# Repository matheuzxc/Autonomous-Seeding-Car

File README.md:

# Autonomous-Seeding-Car

Este projeto visa o desenvolvimento de um veículo remotamente controlado com controle de velocidade variável e navegação autônoma até coordenadas pré-definidas. A funcionalidade adicional será a simulação de uma semeadora automatizada, abordando desafios de sincronização mecânica-eletrônica e mapeamento georreferenciado.

## Metodologia

A metodologia adotada para o desenvolvimento do **Autonomous-Seeding-Car** foca na criação de um sistema autônomo e preciso, que integra controle de navegação, movimentação e semeadura em um veículo de baixo custo. A estrutura metodológica do projeto é composta pelas seguintes etapas principais:

### 1. **Navegação Autônoma**

A navegação do carrinho é baseada em coordenadas geográficas. O veículo utiliza um sistema de GPS para determinar sua posição e calcular a direção necessária para alcançar um destino pré-definido. A direção do carrinho é continuamente corrigida utilizando uma bússola digital, que fornece a orientação do veículo em relação ao norte magnético.

Além disso, o movimento é controlado dinamicamente com base em um sistema de controle, que ajusta a velocidade e a direção das rodas para garantir que o carrinho siga a trajetória desejada. A navegação é baseada na conversão das coordenadas geográficas em distâncias e ângulos de deslocamento, minimizando erros ao longo do caminho.

### 2. **Controle de Velocidade e Deslocamento**

O sistema de controle utiliza um controlador proporcional-integral-derivativo (PID) para ajustar a velocidade e direção do carrinho, de forma a evitar oscilações e garantir uma movimentação suave e precisa. O PID ajuda a manter o carrinho na trajetória correta, mesmo em condições variáveis ou imprecisas de movimentação, resultando em uma navegação mais estável e controlada.

### 3. **Execução da Semeadura**

Quando o carrinho chega ao ponto de destino, o processo de semeadura é automaticamente acionado. O carrinho se move em um padrão sistemático, alternando entre deslocamentos lineares e laterais para cobrir a área predeterminada para semeadura. Durante esses movimentos, o sistema de dispersão libera as sementes de maneira uniforme, assegurando que a operação de semeadura seja realizada de forma eficiente e precisa.

### 4. **Integração Mecânica e Eletrônica**

O projeto envolve desafios significativos de sincronização entre a mecânica e a eletrônica, especialmente na operação do sistema de semeadura e controle de movimentação. O ajuste contínuo de posição e direção, bem como o controle preciso do sistema de semeadura, são feitos de forma coordenada para garantir que as sementes sejam liberadas no momento e local corretos.

### 5. **Mapeamento Georreferenciado**

A navegação do carrinho é suportada por um mapeamento georreferenciado, que permite ao veículo seguir coordenadas pré-definidas, assegurando a cobertura adequada da área. A utilização de dados geoespaciais ajuda a garantir que o carrinho execute a semeadura de forma precisa, mapeando de forma eficiente os locais onde as sementes devem ser dispersas.

---

## Arcadia e Capella

Para o desenvolvimento do projeto, foi utilizada a **metodologia Arcadia** juntamente com a ferramenta **Capella**, ambas voltadas para a modelagem de sistemas complexos.

### Arcadia

**Arcadia** (Architecture Analysis & Design Integrated Approach) é uma metodologia estruturada para a análise e o design de sistemas complexos. Ela permite modelar, definir e validar os requisitos, projetar a arquitetura do sistema e garantir que todos os elementos funcionem de forma coerente e integrada.

A metodologia Arcadia segue um fluxo de camadas, cada uma abordando um aspecto específico do sistema:

1. **Operational Analysis (OA)**: Define as necessidades dos usuários e as operações gerais do sistema.
2. **System Analysis (SA)**: Especifica o que o sistema deve fazer, sem entrar nos detalhes de implementação.
3. **Logical Architecture (LA)**: Estrutura o sistema em componentes lógicos, definindo suas interações.
4. **Physical Architecture (PA)**: Foca na implementação real, especificando o hardware, software e interfaces.

Para o **Autonomous-Seeding-Car**, foi adotada a **camada de Arquitetura Física**, dado o prazo de desenvolvimento ágil e a necessidade de implementação prática dentro de um tempo limitado. Esta camada descreve todos os componentes físicos e suas interações no sistema, garantindo que a arquitetura final seja viável e eficiente.

### Capella

**Capella** é a ferramenta de modelagem baseada na metodologia Arcadia. Ela permite criar diagramas, definir requisitos, especificar as interações entre os módulos e gerar a arquitetura do sistema. Capella proporciona uma visão clara e estruturada de como o sistema será implementado, facilitando a análise e o design, além de garantir a consistência entre os diferentes componentes.

Com Capella, a arquitetura física do **Autonomous-Seeding-Car** foi modelada e validada, permitindo o desenvolvimento e implementação eficiente de todos os módulos do sistema, desde a navegação até a semeadura automatizada.

---

## Diagramas do Sistema

Abaixo estão os diagramas explicativos que foram usados para modelar a arquitetura do sistema no **Capella**.

### Bloco de Componente na Arquitetura Física

Este diagrama mostra os principais blocos de componentes na arquitetura física do **Autonomous-Seeding-Car**, representando os módulos de hardware e suas interações.

### Arquitetura Final

O diagrama abaixo mostra a arquitetura final do sistema, com os componentes integrados e suas conexões, tanto físicas quanto lógicas. Ele ilustra como os diferentes módulos interagem para formar o sistema completo.

---

Com essa abordagem metodológica e a utilização das ferramentas Arcadia e Capella, o projeto **Autonomous-Seeding-Car** é desenvolvido de forma organizada e eficaz, garantindo que todos os componentes funcionem de maneira integrada e otimizando o processo de navegação e semeadura do veículo.

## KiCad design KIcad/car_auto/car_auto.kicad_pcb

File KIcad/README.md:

# PCB do Sistema Eletrônico - **Autonomous-Seeding-Car**

Este repositório contém as PCBs (Placas de Circuito Impresso) que compõem os módulos eletrônicos do projeto **Autonomous-Seeding-Car**. O sistema eletrônico é composto por três PCBs empilhadas verticalmente, cada uma responsável por um conjunto específico de funções dentro do sistema. As PCBs foram projetadas no **KiCad**, com o objetivo de criar um design eficiente e compactado, garantindo a integração correta dos módulos eletrônicos.

## Estrutura das PCBs

A estrutura do sistema é organizada em três PCBs interconectadas, uma em cima da outra, de forma a otimizar o uso de espaço e a organização dos componentes. Cada PCB desempenha um papel crucial no funcionamento geral do carrinho autônomo. As PCBs são distribuídas conforme descrito abaixo:

### PCB 1: Módulo Regulador de Tensão e Ponte H

A primeira PCB contém os seguintes módulos eletrônicos:

- **Módulo Regulador de Tensão (LM2596)**: Responsável por fornecer a tensão estável necessária para os outros módulos do sistema, garantindo que os componentes eletrônicos operem de forma segura e eficiente.
- **Ponte H Dupla (L298N)**: Controla os motores do veículo, regulando a direção e velocidade com base nos comandos enviados pelo ESP32. Este módulo é essencial para o controle de movimentação do carrinho.

### PCB 2: ESP32 e Módulo Bluetooth

A segunda PCB contém os seguintes componentes:

- **ESP32 WROOM**: O microcontrolador central do sistema, que coordena a comunicação entre os diferentes módulos e processa os comandos para controle de movimento e semeadura.
- **Módulo Bluetooth HC-05**: Responsável pela comunicação sem fio com o controle remoto, permitindo que o carrinho seja operado remotamente. Recebe comandos de movimentação e transmite-os ao ESP32 para execução.

### PCB 3: Módulo GPS

A terceira PCB contém o **Módulo GPS NEO-6M**, responsável por fornecer a localização geográfica do carrinho. Ele permite que o veículo se desloque até coordenadas pré-definidas com precisão, essencial para a navegação autônoma.

### Montagem Final das 3 PCBs

As 3 PCBs foram projetadas para serem empilhadas verticalmente, com uma em cima da outra. A disposição otimiza o uso do espaço e facilita a integração dos módulos. Abaixo, está a foto da montagem final das 3 PCBs conectadas.

### Posicionamento da Bússola

A **bússola (HMC5883L)** está posicionada na frente do carro, fora da pilha de PCBs. Ela é responsável por fornecer a direção do carrinho em relação ao norte magnético, permitindo que o sistema ajuste a orientação de forma precisa.

---

## Pinos de Conexão no ESP32

Abaixo estão os pinos utilizados para cada módulo no ESP32:

| **Módulo**           | **Pinos no ESP32**                               |
|----------------------|--------------------------------------------------|
| **GPS (NEO-6M)**      | RX2 → GPIO 16, TX2 → GPIO 17                    |
| **Bússola/IMU**       | SDA → GPIO 21, SCL → GPIO 22                    |
| **Ponte H (Motores)** | IN1 → GPIO 25, IN2 → GPIO 26, IN3 → GPIO 27, IN4 → GPIO 14, PWM A → GPIO 32, PWM B → GPIO 33 |
| **Bluetooth (HC-05)** | RX1 → GPIO 4, TX1 → GPIO 2                      |
| **Servo Motor**       | Sinal → GPIO 13                                 |

---

## Design no KiCad

Todas as PCBs foram projetadas no **KiCad**, uma ferramenta open-source poderosa para o design de circuitos eletrônicos e PCBs. O design foi otimizado para garantir um layout compacto, com o mínimo de interferências entre os componentes e com uma conexão eficiente entre as diferentes placas.

---

## Contribuições

Contribuições para este projeto são bem-vindas! Caso deseje sugerir melhorias no design ou no código, fique à vontade para abrir um **pull request**.

---

## Licença

Este projeto está licenciado sob a licença **MIT**. Consulte o arquivo LICENSE para mais detalhes.

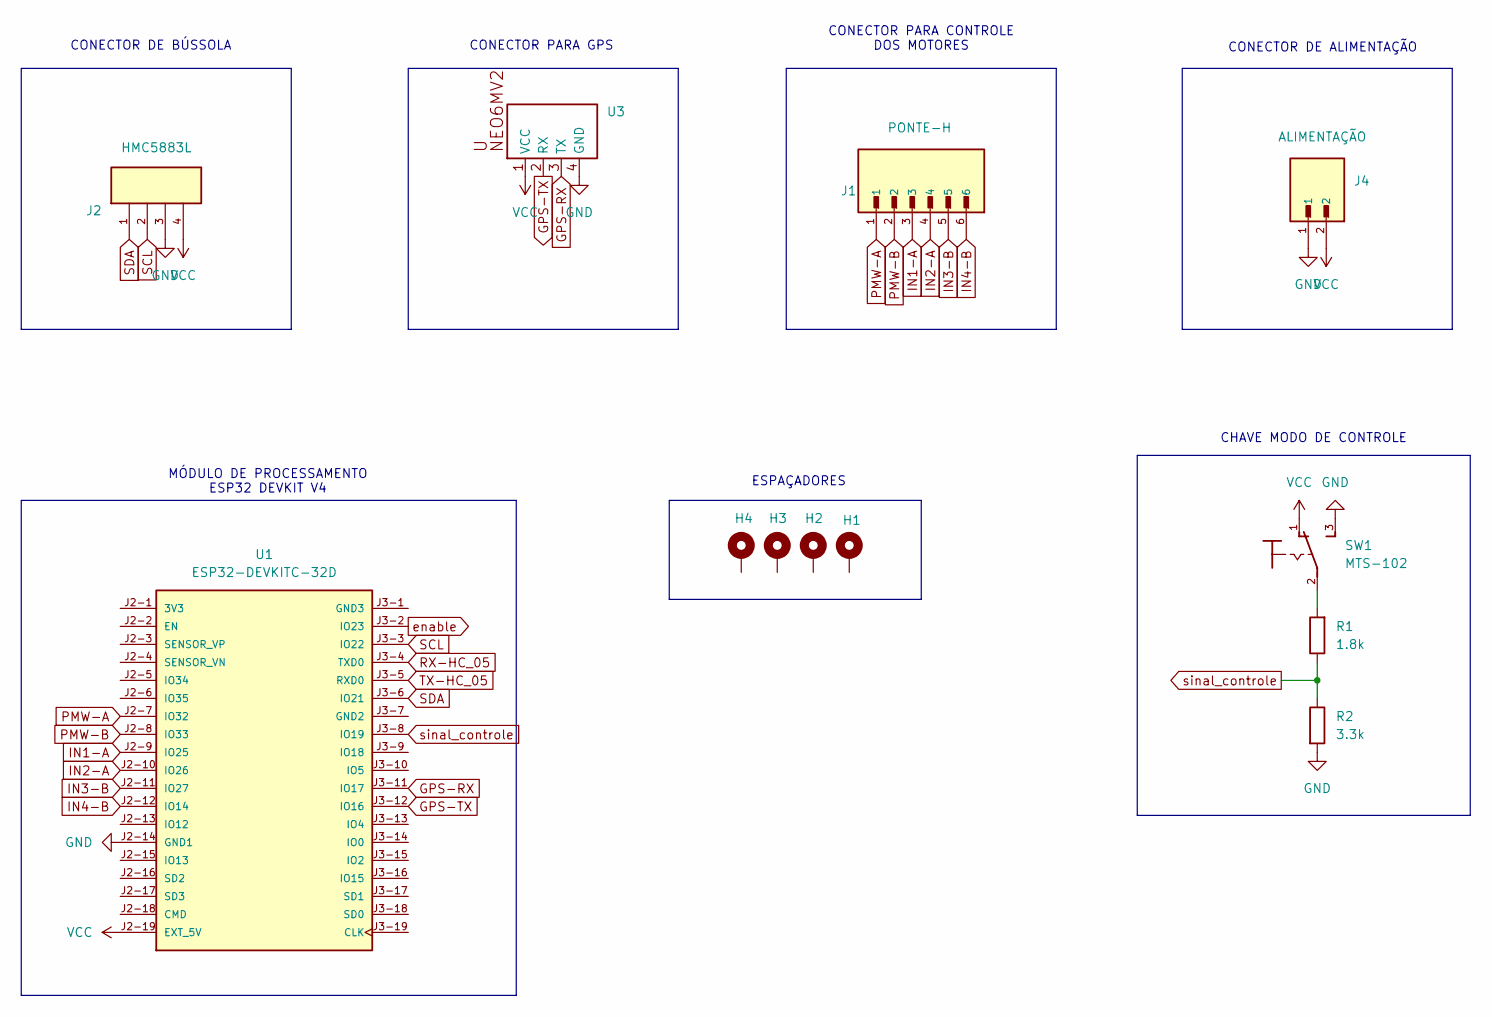
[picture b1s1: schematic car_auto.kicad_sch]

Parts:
H1, H2, H3, H4: MountingHole_Pad; MountingHole_3.2mm_M3_DIN965_Pad
J1: PONTE-H; JST_B6P-VH_LF__SN_
J2: HMC5883L; JST_B4P-VH_LF__SN_
J4: ALIMENTAÇÃO; JST_B2P-VH_LF__SN_
R1: 1.8k; R_Axial_DIN0207_L6.3mm_D2.5mm_P10.16mm_Horizontal
R2: 3.3k; R_Axial_DIN0207_L6.3mm_D2.5mm_P10.16mm_Horizontal
SW1: MTS-102
U1: ESP32-DEVKITC-32D; MODULE_ESP32-DEVKITC-32D; PARTREV V4
U3: NEO-6M-V2-GPSMODULE-FOOTPRINT

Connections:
GND: J2.3, J4.1, R2.2, SW1.3, U1.J2-14 (GND1), U3.4 (GND)
GPS-RX: U1.J3-11 (IO17), U3.3 (TX)
GPS-TX: U1.J3-12 (IO16), U3.2 (RX)
IN1-A: J1.3, U1.J2-9 (IO25)
IN2-A: J1.4, U1.J2-10 (IO26)
IN3-B: J1.5, U1.J2-11 (IO27)
IN4-B: J1.6, U1.J2-12 (IO14)
unnamed: R1.2, SW1.2
PMW-A: J1.1, U1.J2-7 (IO32)
PMW-B: J1.2, U1.J2-8 (IO33)
RX-HC_05: U1.J3-4 (TXD0)
SCL: J2.2, U1.J3-3 (IO22)
SDA: J2.1, U1.J3-6 (IO21)
TX-HC_05: U1.J3-5 (RXD0)
VCC: J2.4, J4.2, SW1.1, U1.J2-19 (EXT_5V), U3.1 (VCC)
enable: U1.J3-2 (IO23)
sinal_controle: R1.1, R2.1, U1.J3-8 (IO19)

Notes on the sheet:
CONECTOR PARA GPS
MÓDULO DE PROCESSAMENTO ESP32 DEVKIT V4
CONECTOR PARA CONTROLE DOS MOTORES
ESPAÇADORES
CONECTOR DE BÚSSOLA
CONECTOR DE ALIMENTAÇÃO
CHAVE MODO DE CONTROLE

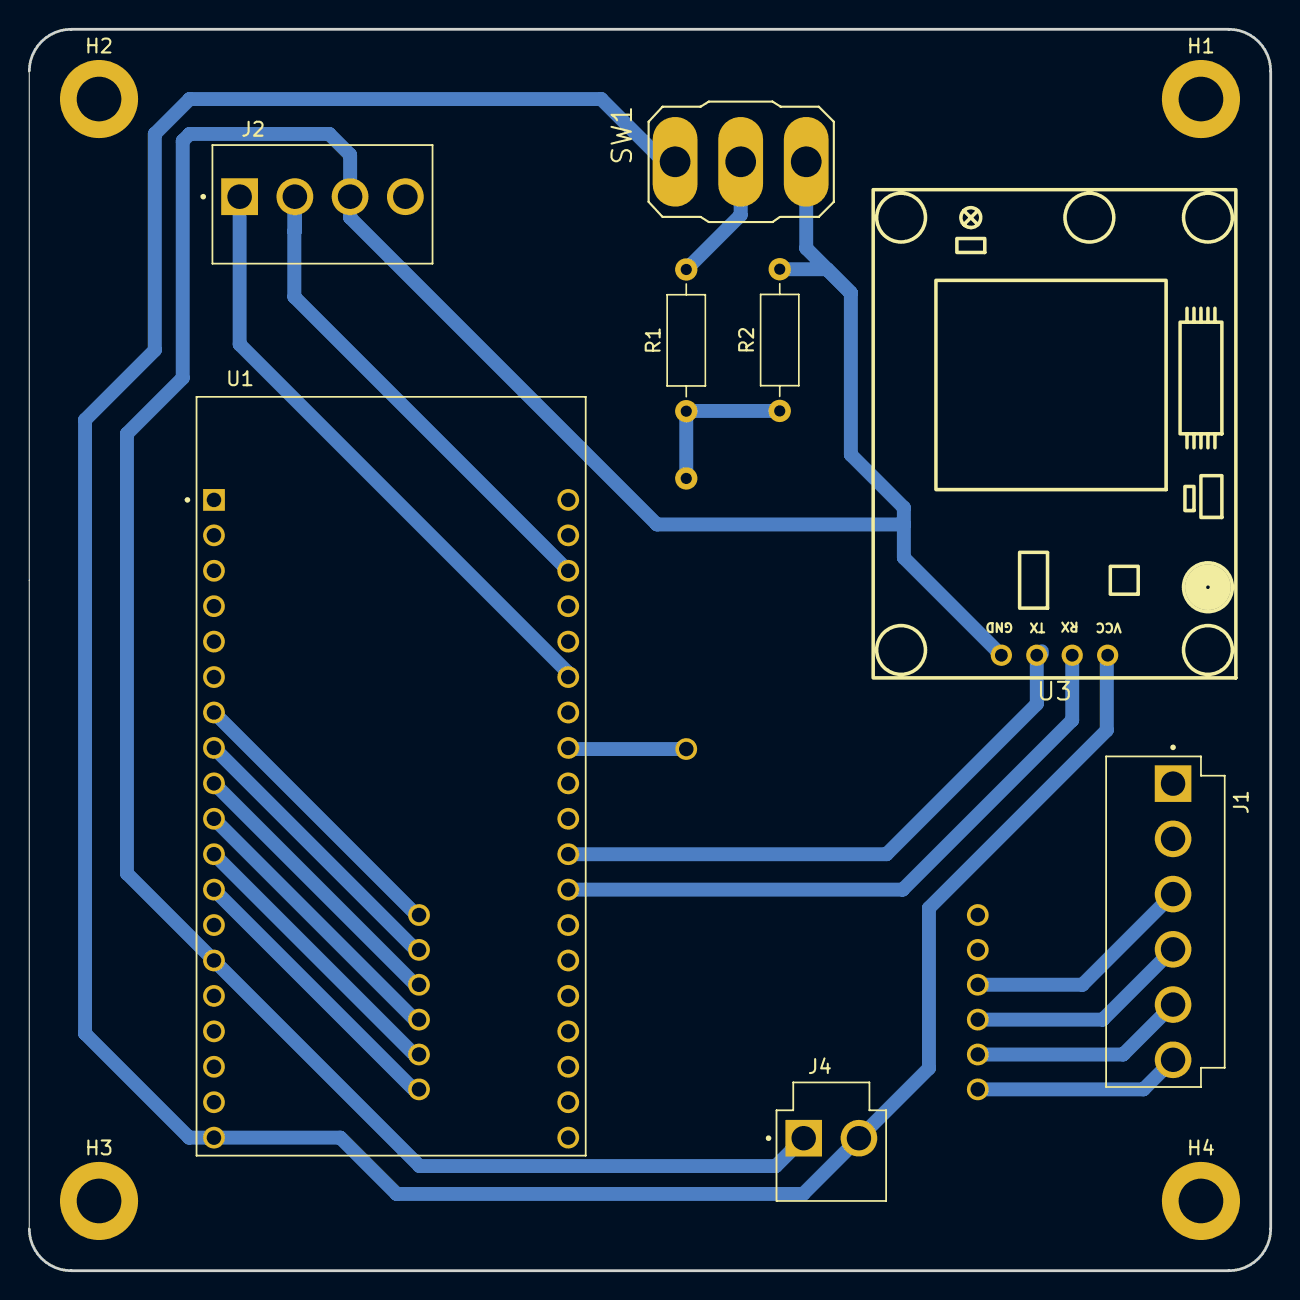
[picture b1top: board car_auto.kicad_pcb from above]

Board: 2 copper layers, 89.0 x 89.0 mm, 12 parts (0 on the bottom side), 14 nets.

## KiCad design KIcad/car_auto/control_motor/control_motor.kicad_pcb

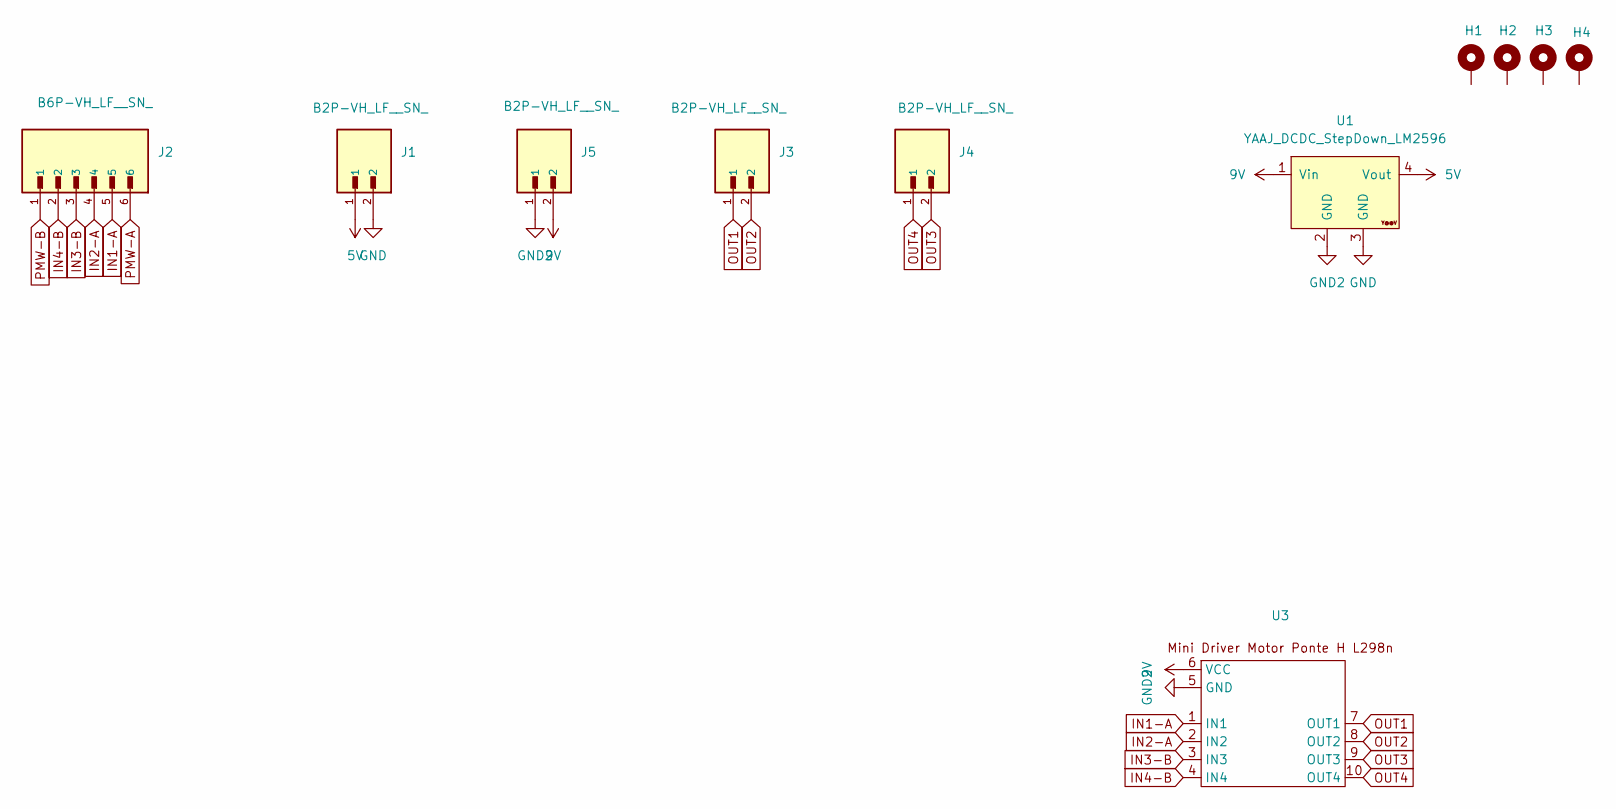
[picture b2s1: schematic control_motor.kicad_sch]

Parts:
H1, H2, H3, H4: MountingHole_Pad; MountingHole_3.2mm_M3_DIN965_Pad
J1, J3, J4, J5: B2P-VH_LF__SN_; JST_B2P-VH_LF__SN_
J2: B6P-VH_LF__SN_; JST_B6P-VH_LF__SN_
U1: YAAJ_DCDC_StepDown_LM2596
U3: Mini Driver Motor Ponte H L298n

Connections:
5V: J1.1, U1.4 (Vout)
9V: J5.2, U1.1 (Vin), U3.6 (VCC)
GND: J1.2, U1.3 (GND)
GND2: J5.1, U1.2 (GND), U3.5 (GND)
IN1-A: J2.5, U3.1 (IN1)
IN2-A: J2.4, U3.2 (IN2)
IN3-B: J2.3, U3.3 (IN3)
IN4-B: J2.2, U3.4 (IN4)
OUT1: J3.1, U3.7 (OUT1)
OUT2: J3.2, U3.8 (OUT2)
OUT3: J4.2, U3.9 (OUT3)
OUT4: J4.1, U3.10 (OUT4)
PMW-A: J2.6
PMW-B: J2.1

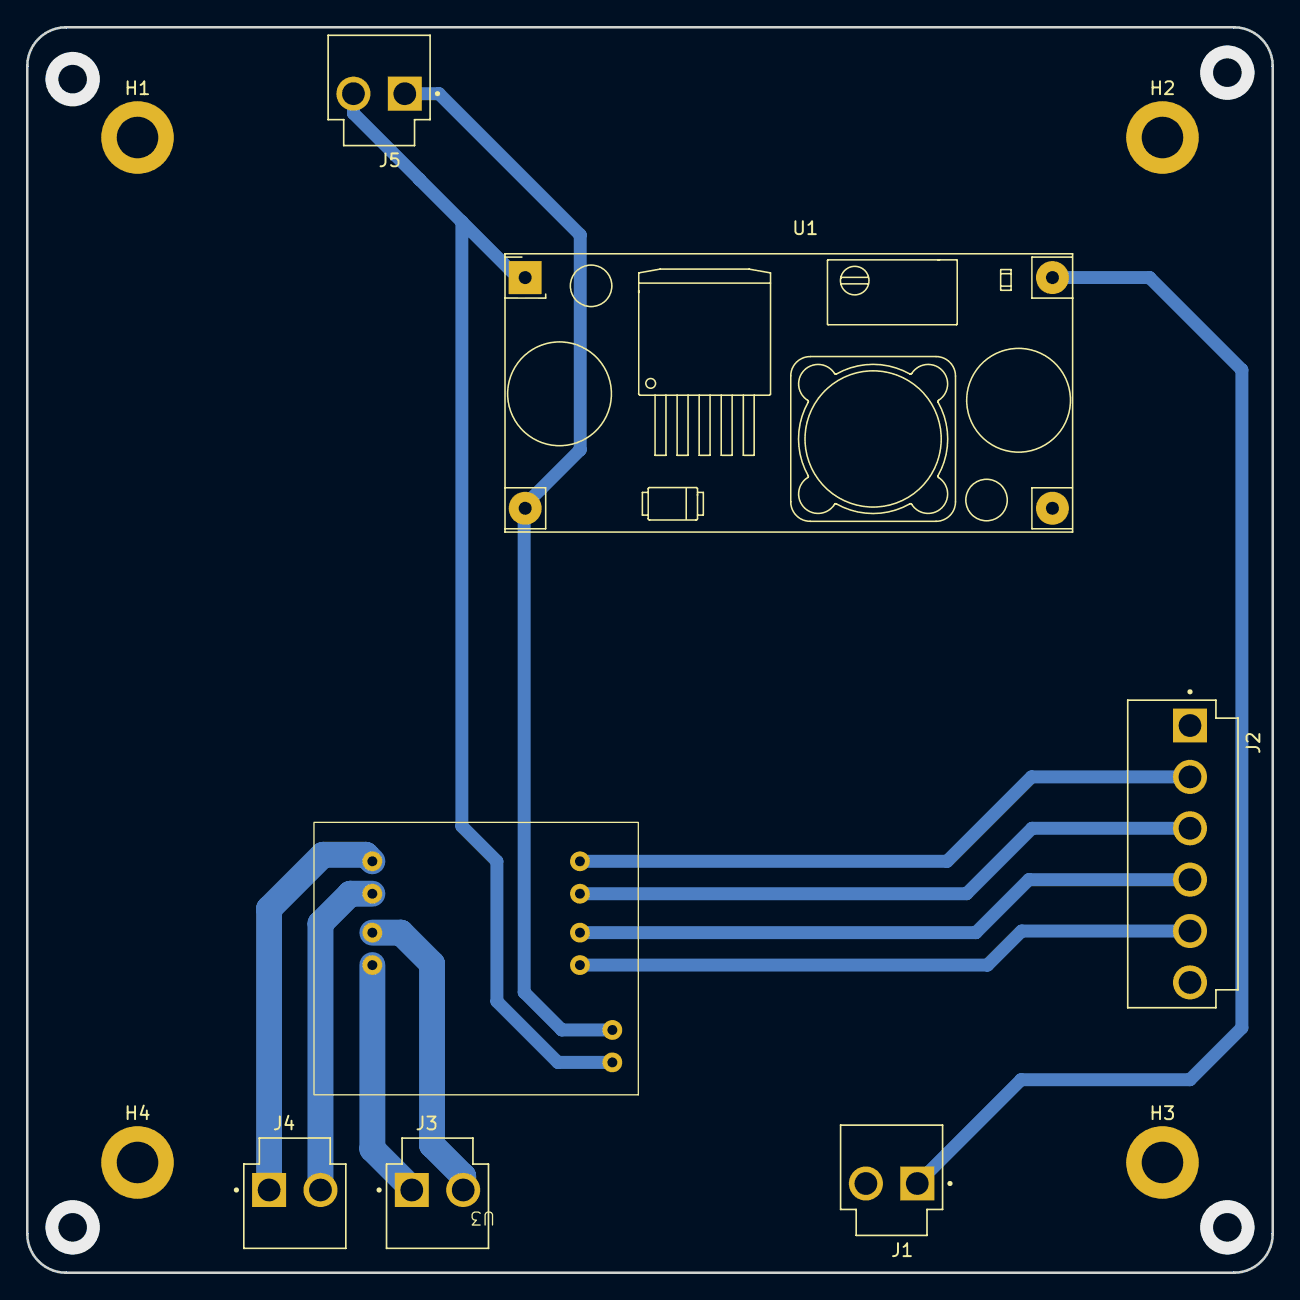
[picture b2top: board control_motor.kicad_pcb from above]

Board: 2 copper layers, 96.0 x 96.0 mm, 11 parts (0 on the bottom side), 12 nets.

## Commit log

2025-03-29 códigos para controle do motor
2025-03-30 adição dos arquivos PCB
2025-03-30 Update README.md
    atualização do readme
2025-03-30 Update README.md
    att readme
2025-04-13 feat: Implementação da classe para controle dos motores via Bluetooth.
2025-04-13 fodase
2025-04-16 enh: Atualizações no código de controle remote.
2025-04-24 codigo_gps
    Código utilizado para pegar posição de gps
2025-05-26 enh: Atualizações no codigo de controle dos motores e controle remoto
2025-06-27 feat: Implement navigation system with compass and motor control
    - Added Bussola class for compass handling with filtering.
    - Introduced Motor class for H-bridge motor control with PWM support.
    - Created Navigator class to manage robot navigation and movement towards targets.
    - Implemented GPS functionality for location tracking and filtering.
    - Updated main loop to integrate navigation and movement logic.
    - Refactored control_motor methods to use PWM for speed control.
